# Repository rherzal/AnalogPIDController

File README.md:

# This is the main repository for my measurements and actuators semester project

The project is a full design and implementation of an analog PID controller pcb, using only operational amplifiers for calculations, used to control a DC motor.

It uses 3 potentiometers for setting the 3 controller constants, one potentiometer for setting the command signal, and one potentiometer for angular feedback.

The PCB was manufactured with the help of a local electronics company from Baia Mare, [circuite-imprimate.ro](https://circuite-imprimate.ro/).

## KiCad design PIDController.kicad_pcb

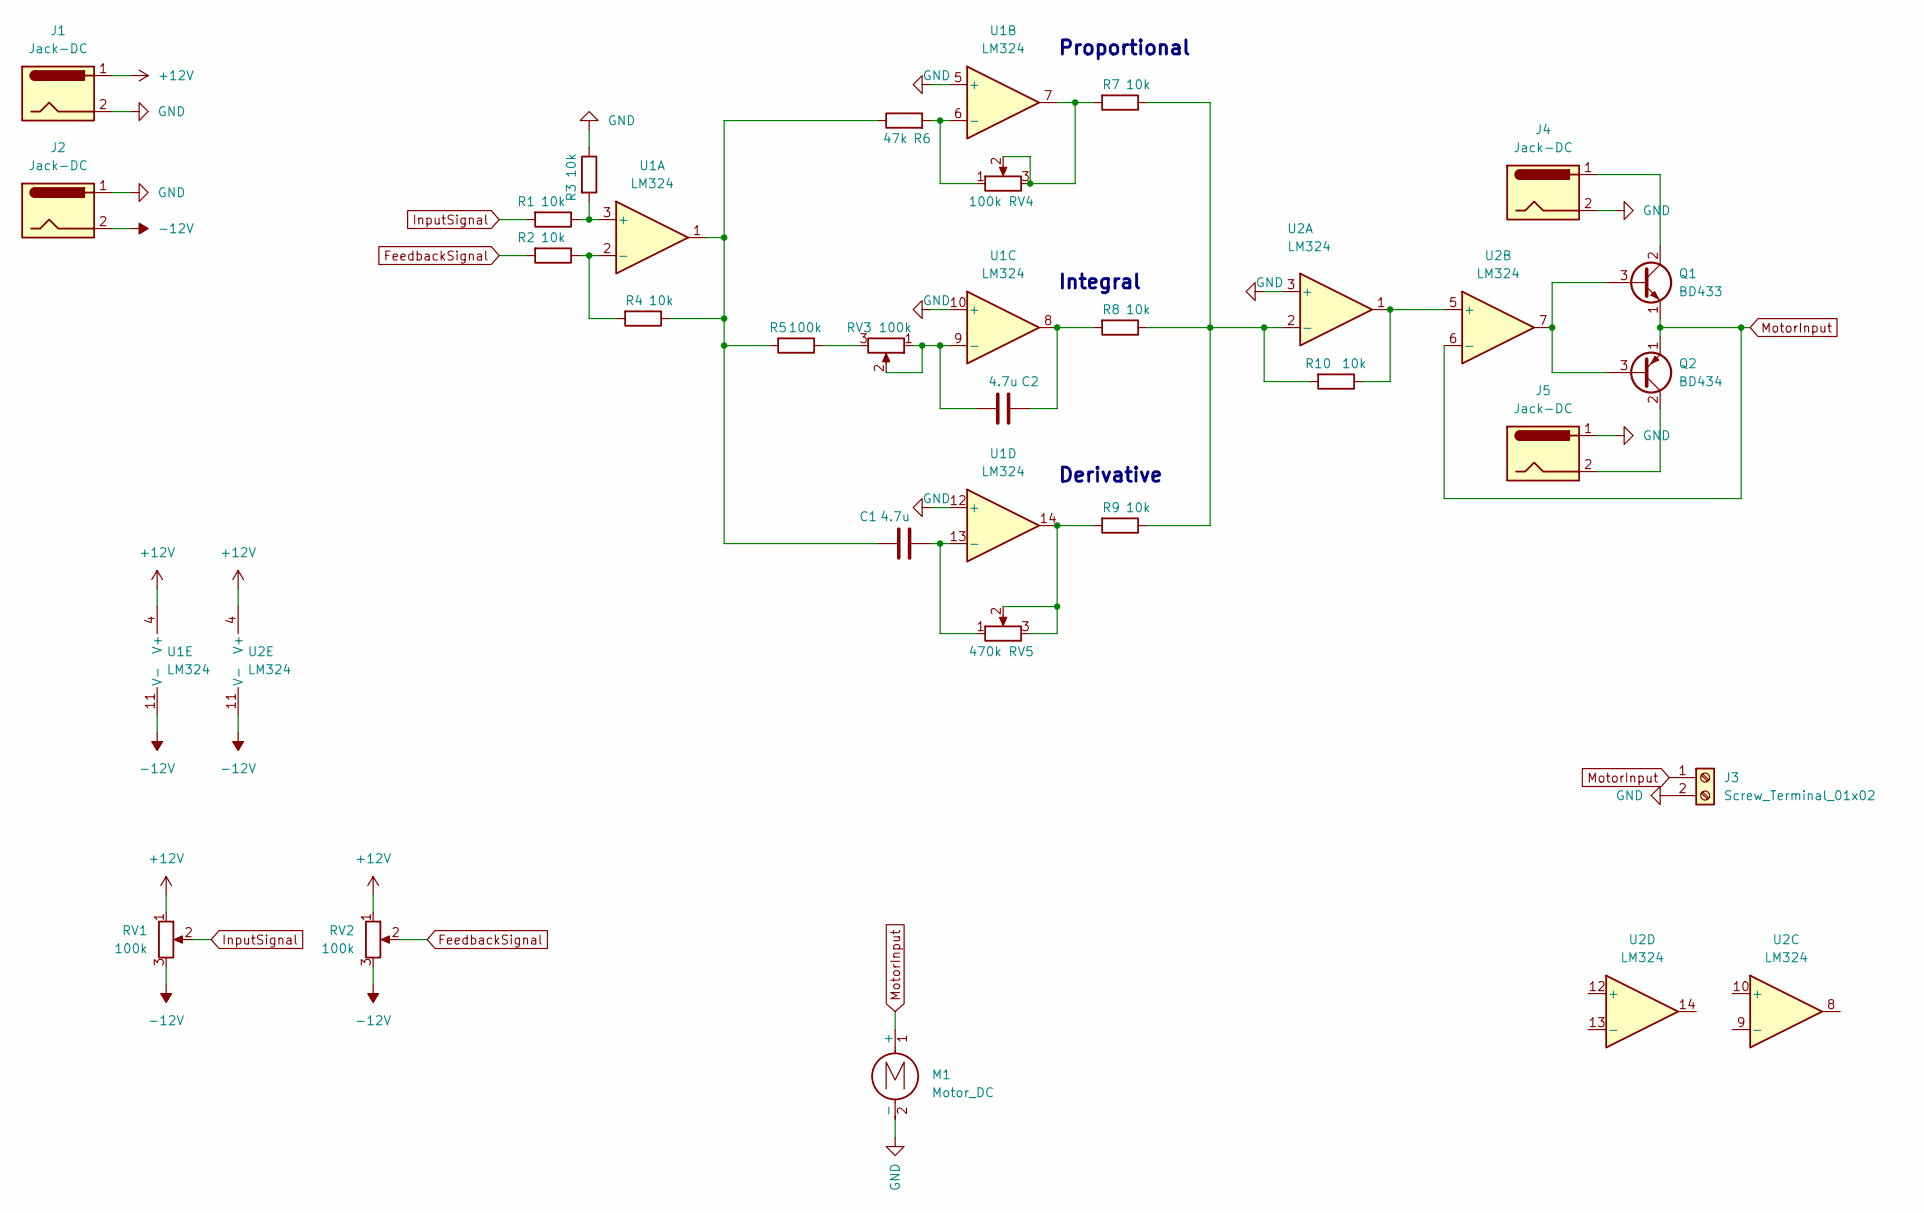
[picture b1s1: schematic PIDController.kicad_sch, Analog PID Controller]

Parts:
C1, C2: 4.7u; C_Rect_L4.6mm_W3.8mm_P2.50mm_MKS02_FKP02
J1, J2, J4, J5: Jack-DC; BarrelJack_GCT_DCJ200-10-A_Horizontal
J3: Screw_Terminal_01x02; TerminalBlock_RND_205-00001_1x02_P5.00mm_Horizontal
M1: Motor_DC; TerminalBlock_RND_205-00001_1x02_P5.00mm_Horizontal
Q1: BD433; TO-126-3_Vertical
Q2: BD434; TO-126-3_Vertical
R1, R2, R3, R4, R7, R8, R9, R10: 10k; R_Axial_DIN0207_L6.3mm_D2.5mm_P15.24mm_Horizontal
R5: 100k; R_Axial_DIN0207_L6.3mm_D2.5mm_P15.24mm_Horizontal
R6: 47k; R_Axial_DIN0207_L6.3mm_D2.5mm_P15.24mm_Horizontal
RV1, RV2, RV3, RV4: 100k; Potentiometer_Piher_PC-16_Single_Horizontal
RV5: 470k; Potentiometer_Piher_PC-16_Single_Horizontal
U1, U2: LM324; DIP-14_W7.62mm_Socket

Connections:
+12V: J1.1, RV1.1, RV2.1, U1.4 (V+), U2.4 (V+)
-12V: J2.2, RV1.3, RV2.3, U1.11 (V-), U2.11 (V-)
FeedbackSignal: R2.2, RV2.2
GND: J1.2, J2.1, J3.2, J4.2, J5.1, M1.2 (-), R3.1, U1.5 (+), U1.10 (+), U1.12 (+), U2.3 (+)
InputSignal: R1.2, RV1.2
MotorInput: J3.1, M1.1 (+), Q1.1 (E), Q2.1 (E), U2.6 (-)
unnamed: C1.1, R4.1, R5.2, R6.1, U1.1
unnamed: C1.2, RV5.1, U1.13 (-)
unnamed: C2.1, RV3.1, RV3.2, U1.9 (-)
unnamed: C2.2, R8.2, U1.8
unnamed: J4.1, Q1.2 (C)
unnamed: J5.2, Q2.2 (C)
unnamed: Q1.3 (B), Q2.3 (B), U2.7
unnamed: R1.1, R3.2, U1.3 (+)
unnamed: R2.1, R4.2, U1.2 (-)
unnamed: R5.1, RV3.3
unnamed: R6.2, RV4.1, U1.6 (-)
unnamed: R7.2, RV4.2, RV4.3, U1.7
unnamed: R9.2, RV5.2, RV5.3, U1.14
unnamed: R10.1, U2.1, U2.5 (+)
unnamed: R7.1, R8.1, R9.1, R10.2, U2.2 (-)

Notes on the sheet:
Proportional
Integral
Derivative

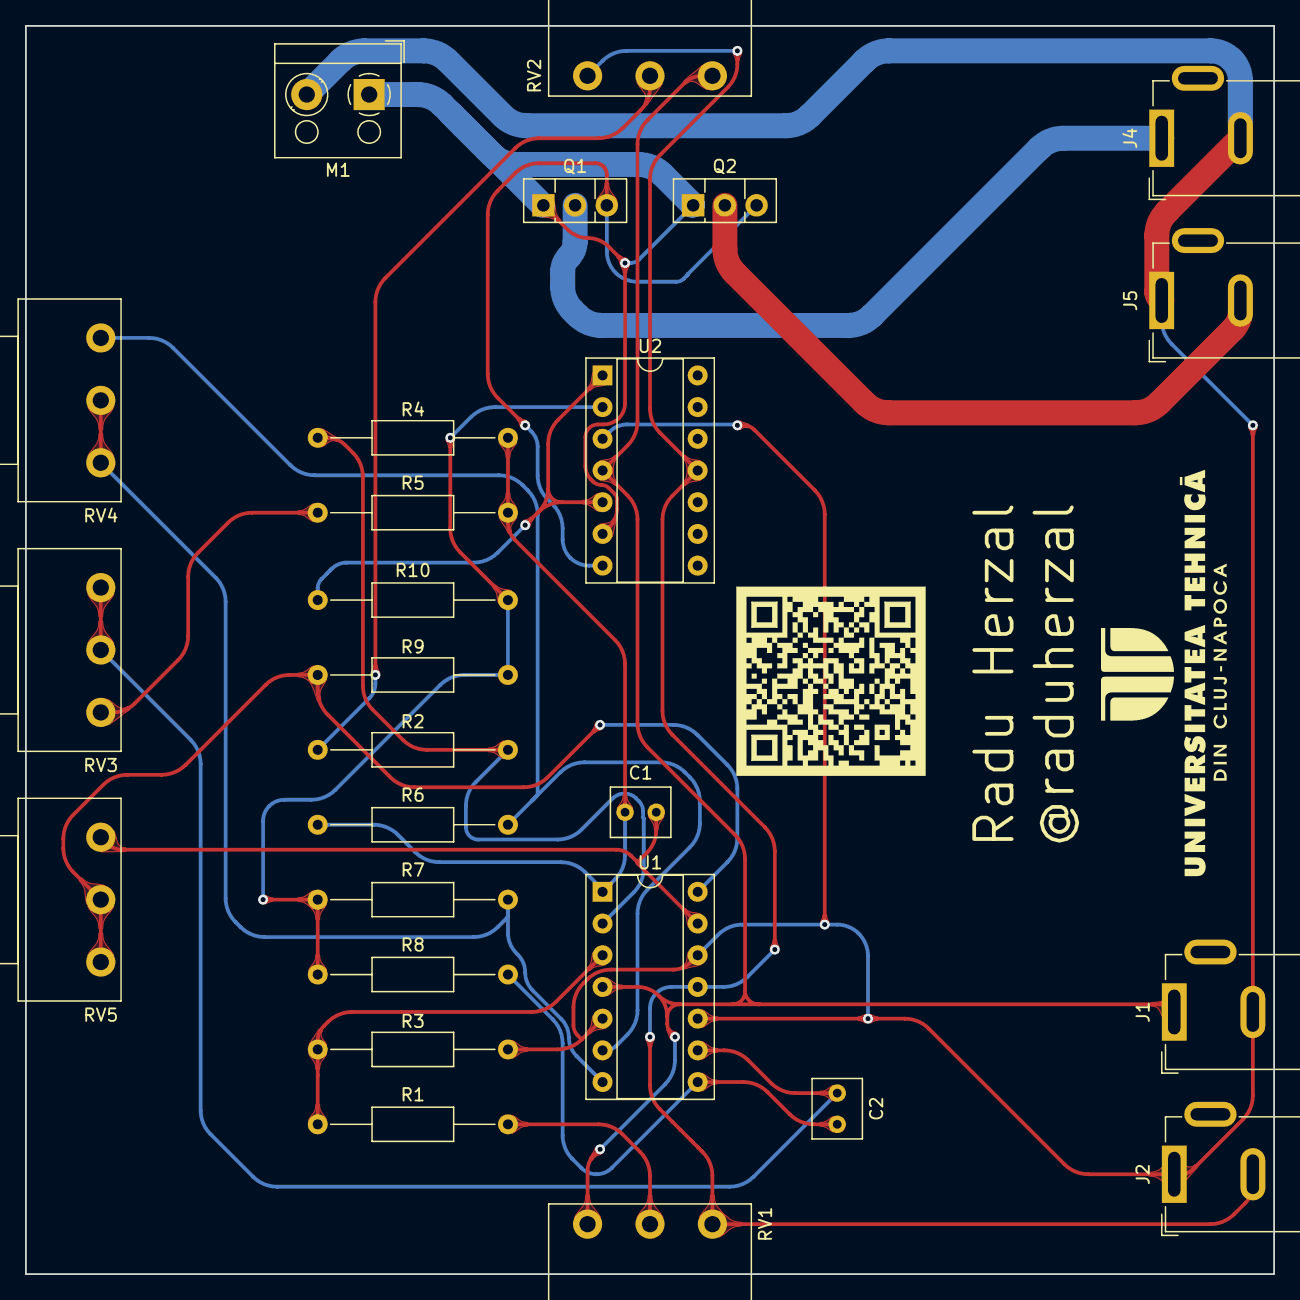
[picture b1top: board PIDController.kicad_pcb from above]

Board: 2 copper layers, 100.0 x 100.0 mm, 26 parts (0 on the bottom side), 21 nets.

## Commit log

2022-11-06 improved the general design, added ground plane, silkmask etc.
2022-11-06 changed sponsor link
